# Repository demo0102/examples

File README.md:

Examples
========

Here you will find PCB examples made using QEDA.

Wi-Fi Adapter
-------------

This is a simple adapter allowing to connect **ESP-07** Wi-Fi module to **Pixhawk** autopilot.

- EDA: [KiCad](http://kicad-pcb.org/)
- Source: [./wifi-adapter](./wifi-adapter)

Licence
=======

All source files are licensed under [MIT license](./LICENSE).

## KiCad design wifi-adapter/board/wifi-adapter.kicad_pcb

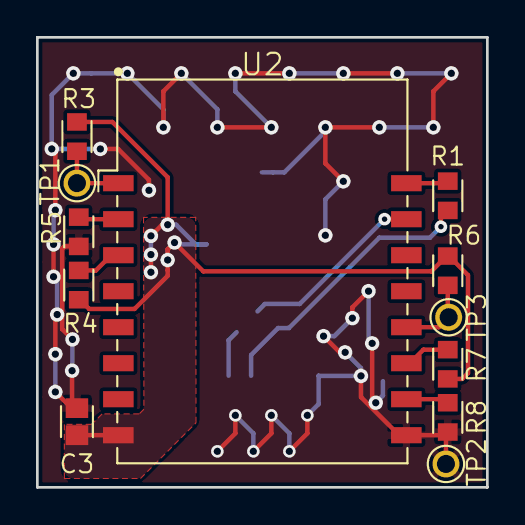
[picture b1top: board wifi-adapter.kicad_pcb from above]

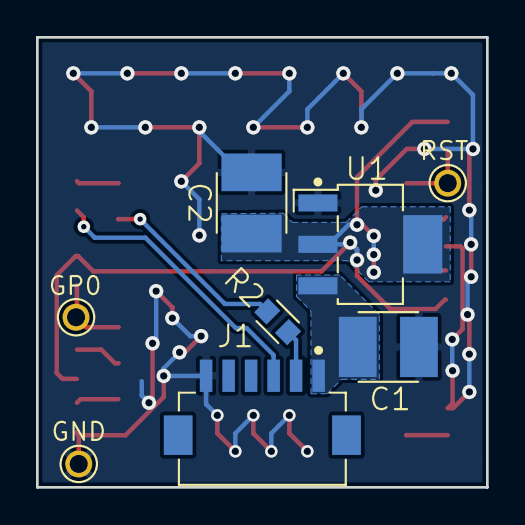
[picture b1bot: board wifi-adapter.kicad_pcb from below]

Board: 2 copper layers, 25.0 x 25.0 mm, 17 parts (5 on the bottom side), 13 nets.

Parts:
C1, C2: 10u; CAPC3225X230M
C3: 0.1u; CAPC1608X92M
J1: DF13A-6P-1.25H; HIROSE_DF13A-6P-1.25H
R1, R2: 33; RESC1608X55M
R3, R5, R6, R7: DNP; RESC1608X55M
R4, R8: 10k; RESC1608X55M
TP1: RST; TP-TH-1
TP2: GND; TP-TH-1
TP3: GP0; TP-TH-1
U1: LM1117IMPX-3.3; SOT230P700X180-4M
U2: ESP-07; SON200P2120X1600X300-16M

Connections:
+3V3: C2.1, C3.1, R3.1, R4.1, R6.2, R7.2, U1.2, U1.4, U2.8
+5V: C1.2, J1.1, U1.3
/TELEM_RX: J1.3, R1.1
/TELEM_TX: J1.2, R2.1
GND: C1.1, C2.2, C3.2, J1.6, R5.1, R8.2, TP2.1, U1.1, U2.9
unnamed: R1.2, U2.16
unnamed: R2.2, U2.15
unnamed: R3.2, TP1.1, U2.1
unnamed: R4.2, U2.3
unnamed: R5.2, U2.2
unnamed: R6.1, TP3.1, U2.12
unnamed: R7.1, U2.11
unnamed: R8.1, U2.10

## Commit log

2016-06-12 Add GOST style schematic and gerber files
2016-08-14 Update to actual version
2016-08-14 Minor improvements
2016-09-04 Minor fixes in resistor values
